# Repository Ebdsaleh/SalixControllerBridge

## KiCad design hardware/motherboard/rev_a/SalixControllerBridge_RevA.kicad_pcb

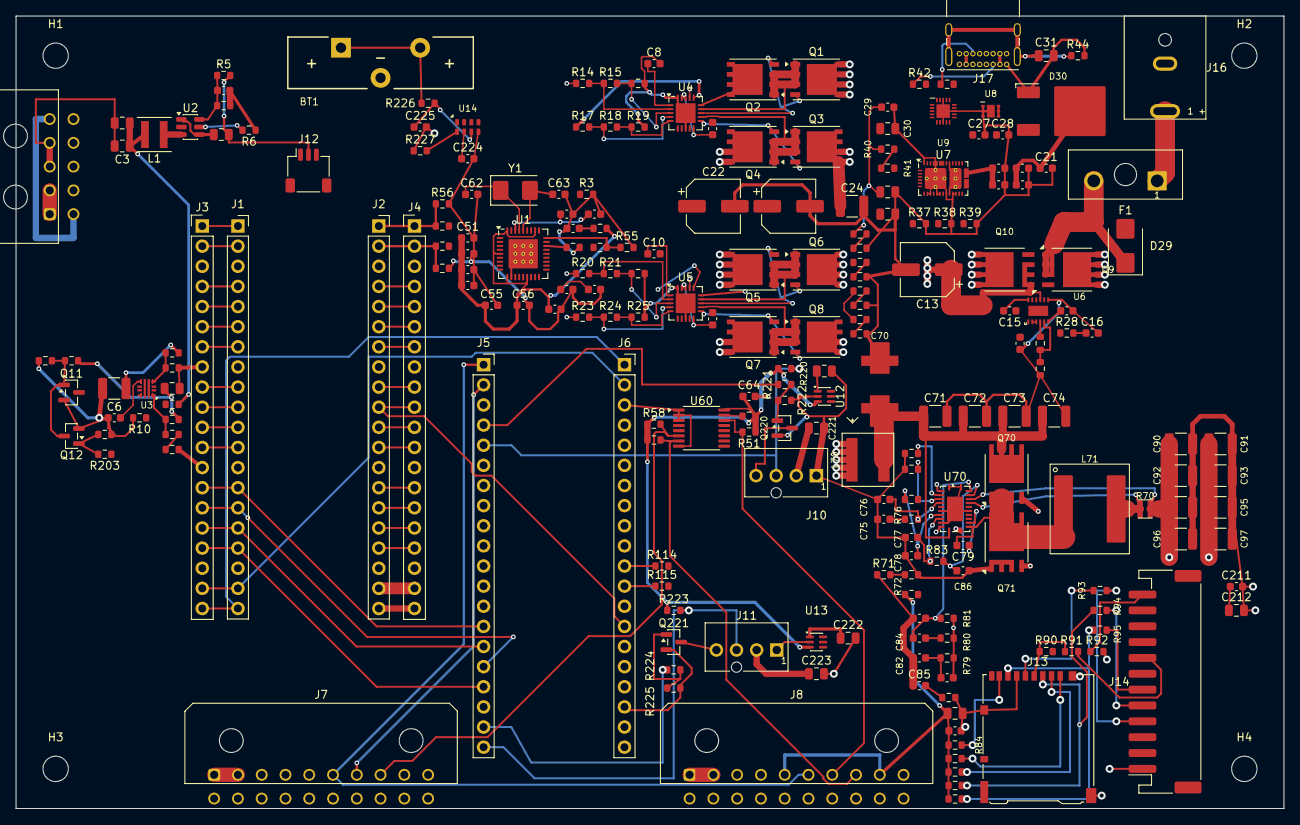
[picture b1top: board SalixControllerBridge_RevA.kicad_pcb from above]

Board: 4 copper layers, 160.0 x 100.0 mm, 230 parts (0 on the bottom side), 187 nets.

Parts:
BT1: CR2032; Keystone_1174_CR2032_Vertical_Exact
C1: 4.7uF 10V X7R; C_0805_2012Metric
C2, C3: 22uF 10V X7R; C_0805_2012Metric
C4: 6.8pF; C_0603_1608Metric
C5: 1uF 35V X7R; C_0805_2012Metric
C6: 10uF 35V X7R; C_1210_3225Metric
C7: 3.3nF 50V; C_0603_1608Metric
C8, C10: 1nF 50V; C_0603_1608Metric
C9, C11: 100nF 10V X7R; C_0603_1608Metric
C12, C14: 100nF 100V X7R; C_0603_1608Metric
C13: EEETQV470XAP 47uF 35V; CP_Elec_6.3x7.7
C15: 100nF 25V X7R; C_0603_1608Metric
C16: 10nF 50V X7R; C_0603_1608Metric
C17: 4.7uF 35V X5R +/-10%; C_0603_1608Metric
C18, C19, C20, C21: 10nF 50V X7R +/-5%; C_0603_1608Metric
C22, C23: 33uF 50V HYBRID +/-20%; CP_Elec_6.3x7.7
C24: 10uF 50V X7R +/-10%; C_1210_3225Metric
C25, C26: 10uF 10V X7R +/-10%; C_0805_2012Metric
C27, C28: 330pF C0G; C_0603_1608Metric
C29: 1uF 35V X5R +/-10%; C_0603_1608Metric
C30, C31: 100nF 100V X7R +/-10%; C_0805_2012Metric
C50: 1uF 10V X7R; C_0603_1608Metric
C51, C52, C53, C54, C56, C57: 100nF X7R; C_0603_1608Metric
C55: 1uF X7R; C_0603_1608Metric
C58, C60: DNP; C_0603_1608Metric
C59, C61: 100nF low-ESR; C_0603_1608Metric
C62, C63: CC0603JRNPO9BN180 18pF C0G; C_0603_1608Metric
C64, C80, C211, C224, C225: 100nF; C_0603_1608Metric
C70: 100uF 35V hybrid; Panasonic_EEH_ZC_F_VibrationProof_8x10.5mm
C71, C72, C73, C74: 10uF 50V X7S; C_1210_3225Metric
C75: 10nF; C_0603_1608Metric
C76: 22pF DNP; C_0603_1608Metric
C77: 2.2uF; C_0603_1608Metric
C78, C79: 0.1uF; C_0603_1608Metric
C81: 0.1uF CSEN; C_0603_1608Metric
C82: 0.47uF CINJ; C_0603_1608Metric
C83: 0.22uF CDAMP; C_0603_1608Metric
C84: 1nF CAEFC; C_0603_1608Metric
C85: 0.1uF CINC; C_0603_1608Metric
C86: 2.2uF CAEFVDD; C_0603_1608Metric
C90, C91, C92, C93, C94, C95, C96, C97: 47uF 10V X7S; C_1210_3225Metric
C210, C212, C221, C223: 10uF; C_0805_2012Metric
C220, C222: 1uF; C_0805_2012Metric
D29: SMBJ36CA; D_SMB
D30: STPS5H100BY-TR; ST_DPAK_STPS5H100Y
F1: MINI FL1 HOLDER / 7.5A PROVISIONAL; Littelfuse_178.6764.0001_MINI_FL1
H1, H2, H3, H4: Salix_MountingHole_3.2mm_M3
J1: PICO-A SOCKET LEFT 1-20; PinSocket_1x20_P2.54mm_Vertical
J2: PICO-A SOCKET RIGHT 21-40; Salix_PinSocket_1x20_P2.54mm_Vertical_P21-40
J3: RAW BREAKOUT 1-20; PinHeader_1x20_P2.54mm_Vertical
J4: RAW BREAKOUT 21-40; Salix_PinHeader_1x20_P2.54mm_Vertical_P21-40
J5: PICO-B SOCKET LEFT 1-20; PinSocket_1x20_P2.54mm_Vertical
J6: PICO-B SOCKET RIGHT 21-40; Salix_PinSocket_1x20_P2.54mm_Vertical_P21-40
J7: PRIMARY FRONT BOARD IF; Molex_Micro-Fit_3.0_43045-2000_2x10_P3.00mm_Horizontal
J8: EXTENDED FRONT BOARD IF; Molex_Micro-Fit_3.0_43045-2000_2x10_P3.00mm_Horizontal
J10: FAN0 — MOLEX 47053-1000; Molex_47053-1000_1x04_P2.54mm_Vertical
J11: FAN1 — MOLEX 47053-1000; Molex_47053-1000_1x04_P2.54mm_Vertical
J12: PICO-A SWD JST-SH; JST_SH_SM03B-SRSS-TB_1x03-1MP_P1.00mm_Horizontal
J13: HIROSE DM3AT-SF-PEJM5; Hirose_DM3AT-SF-PEJM5_Exact
J14: JST S12B-PH-SM4-TB; JST_PH_S12B-PH-SM4-TB_1x12-1MP_P2.00mm_Horizontal
J15: AUX POWER MODULE — MOLEX 43045-1000; Molex_Micro-Fit_3.0_43045-1000_2x05_P3.00mm_Horizontal
J16: KLDHCX-8-0202-B; Kycon_KLDHCX-8-0202-B
J17: USB-C PD POWER — GCT USB4085-GF-A; GCT_USB4085_Exact
L1: XAL4020-222ME 2.2uH; L_Coilcraft_XxL4020
L70: XGL6060-102MEC 1.0uH; Coilcraft_XGL6060_6.71x6.51mm
L71: XGL1010-222MED 2.2uH; Coilcraft_XGL1010_11.3x10.0mm
Q1, Q2, Q3, Q4, Q5, Q6, Q7, Q8: Si7155DP-T1-GE3; Vishay_PowerPAK_SO-8_Single
Q9, Q10: IAUC100N08S5N034ATMA1; Infineon_PG_TDSON_8_34
Q11, Q12: 2N7002BK,215; SOT-23
Q70, Q71: IAUC60N04S6L039; Infineon_PG_TDSON_8_33
Q220, Q221: 2N7002; SOT-23
R1, R2: 22R 1%; R_0603_1608Metric
R3: 12.0k 1%; R_0603_1608Metric
R4: 453k 1%; R_0603_1608Metric
R5, R13, R52, R54, R55, R200, R201, R202: 100k 1%; R_0603_1608Metric
R6: 100k PG pull-up; R_0603_1608Metric
R7: 464k 1%; R_0603_1608Metric
R8: 52.3k 1%; R_0603_1608Metric
R9, R18: 30.1k 1%; R_0603_1608Metric
R10: 1.33k 1%; R_0603_1608Metric
R11, R16, R24: 56.2k 1%; R_0603_1608Metric
R12, R53, R203: 10k 1%; R_0603_1608Metric
R14, R20, R23: 887k 1%; R_0603_1608Metric
R15: 61.9k 1%; R_0603_1608Metric
R17: 931k 1%; R_0603_1608Metric
R19, R22: 44.2k 1%; R_0603_1608Metric
R21: 80.6k 1%; R_0603_1608Metric
R25: 60.4k 1%; R_0603_1608Metric
R26: 93.1k 1%; R_0603_1608Metric
R27: 6.19k 1%; R_0603_1608Metric
R28: 100R 1%; R_0603_1608Metric
R29, R32, R33, R35: 162k 1%; R_0603_1608Metric
R30, R34, R36: 38.0k 1%; R_0603_1608Metric
R31: 38.3k 1%; R_0603_1608Metric
R37, R38, R39, R40, R58, R59, R220, R223, R227: 10k; R_0603_1608Metric
R41, R42, R43: 0R; R_0603_1608Metric
R44: 330R; R_0603_1608Metric
R50, R51: 4.7k 1%; R_0603_1608Metric
R56, R57: 15k 1%; R_0603_1608Metric
R70: 3mR 1% 1W; Susumu_KRL2012E_0508_LongSide
R71, R74: 49.9k 1%; R_0603_1608Metric
R72: 8.06k 1%; R_0603_1608Metric
R73: 24.9k 1%; R_0603_1608Metric
R75: 41.2k 1%; R_0603_1608Metric
R76: 5.90k 1%; R_0603_1608Metric
R78, R92, R222, R225: 100k; R_0603_1608Metric
R79: 17.8R RDAMP; R_0603_1608Metric
R80: 1k RAEFC; R_0603_1608Metric
R81: 49.9k RAEFDC; R_0603_1608Metric
R82: 0.47R RINC; R_0603_1608Metric
R83: 3R RAEFVDD; R_0603_1608Metric
R84, R90, R91, R210, R211, R212, R213: 47k; R_0603_1608Metric
R93, R94, R95: 33R; R_0603_1608Metric
R114, R115: 100R; R_0603_1608Metric
R221, R224: 1k; R_0603_1608Metric
R226: 470R; R_0603_1608Metric
U1: USB2514B/M2; QFN-36-1EP_6x6mm_P0.5mm_EP3.7x3.7mm_ThermalVias
U2: TLV62569P; SOT-23-6
U3: TPS259474LRPWR; TI_RPW0010A_VQFN-HR-10_2x2mm_P0.475mm
U4, U5: LTC4418IUF#PBF; QFN-20-1EP_4x4mm_P0.5mm_EP2.5x2.5mm
U6: LM74800QDRRRQ1; TI_DRR0012E_WSON-12_3x3mm_P0.5mm_FloatingEP
U7: TPS25730ADREFR; TI_REF0038A_WQFN-38-2EP_6x4mm_P0.4
U8: TVS2200DRVR; TI_DRV0006A_WSON-6_2x2mm_P0.65mm_EP1x1.6mm
U9: TPD4S201RUKR; TI_RUK0020B_WQFN-20_3x3mm_P0.4mm_EP1.7x1.7mm
U12, U13: TPS22919DCK; SOT-363_SC-70-6
U14: RV-3028-C7; MicroCrystal_RV-3028-C7
U60: TCA9534APWR; TSSOP-16_4.4x5mm_P0.65mm
U70: LM25149QRGYRQ1; Texas_RGY_R-PVQFN-N24_EP2.05x3.1mm
Y1: CTS 445I25A24M00000 24MHz 10pF; Crystal_SMD_5032-2Pin_5.0x3.2mm

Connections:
3V3_AUX: C2.1, C3.1, C4.1, C51.1, C52.1, C53.1, C54.1, C55.1, C56.1, C57.1, C64.1, C80.1, C210.1, C211.1, C212.1, C224.1, J7.5 (3V3_AUX), J8.5 (3V3_AUX), J8.9 (BOARD_ID), J13.4 (VDD), J14.2 (3V3_LOGIC), L1.2, R4.1, R6.1, R13.2, R50.1, R51.1, R53.1, R58.1, R59.1, R78.1, R84.1, R90.1, R91.1, R210.1, R211.1, R212.1, R213.1, R220.1, R223.1, U1.5 (VDDA33), U1.10 (VDDA33), U1.15 (VDD33), U1.23 (VDD33), U1.29 (VDDA33), U1.36 (VDDA33), U12.3 (ON), U13.3 (ON), U14.7 (VDD), U60.16 (VCC)
3V3_AUX_PG: R6.2, U2.5 (PG)
5V_MAIN: C1.1, C90.1, C91.1, C92.1, C93.1, C94.1, C95.1, C96.1, C97.1, C220.1, C222.1, J2.39 (VSYS), J4.39 (VSYS), J6.39 (VSYS), J7.1 (5V_A), J7.2 (5V_B), J8.1 (5V_A), J8.2 (5V_B), J14.3 (5V_AUX), R54.1, R70.2, U2.1 (EN), U2.4 (VIN), U12.1 (IN), U13.1 (IN), U70.16 (VCCX), U70.21 (VOUT)
5V_MAIN_PGOOD: R78.2, U70.17 (PG/SYNCOUT)
/5V_MAIN / 12A SYNCHRONOUS BUCK/AEF_COMP_MID: C84.2, R80.1
/5V_MAIN / 12A SYNCHRONOUS BUCK/AEF_DAMP_TOP: C82.2, C83.1, R79.1
/5V_MAIN / 12A SYNCHRONOUS BUCK/AEF_RINC_MID: C85.2, R82.1
/5V_MAIN / 12A SYNCHRONOUS BUCK/BUCK_AEFVDDA: C86.1, R83.2, U70.22 (AEFVDDA)
/5V_MAIN / 12A SYNCHRONOUS BUCK/BUCK_CBOOT: C79.1, U70.15 (CBOOT)
/5V_MAIN / 12A SYNCHRONOUS BUCK/BUCK_CNFG: R75.1, U70.3 (CNFG)
/5V_MAIN / 12A SYNCHRONOUS BUCK/BUCK_COMP: C76.1, R76.1, U70.5 (EXTCOMP)
/5V_MAIN / 12A SYNCHRONOUS BUCK/BUCK_COMP_RC: C75.1, R76.2
/5V_MAIN / 12A SYNCHRONOUS BUCK/BUCK_EN: R71.2, R72.1, U70.19 (EN)
/5V_MAIN / 12A SYNCHRONOUS BUCK/BUCK_FB: R73.2, U70.6 (FB)
/5V_MAIN / 12A SYNCHRONOUS BUCK/BUCK_HO: Q70.4 (G), U70.13 (HO)
/5V_MAIN / 12A SYNCHRONOUS BUCK/BUCK_INJ: C83.2, R79.2, R80.2, R81.2, U70.2 (INJ)
/5V_MAIN / 12A SYNCHRONOUS BUCK/BUCK_ISNS_PLUS: L71.2, R70.1, U70.20 (ISNS+)
/5V_MAIN / 12A SYNCHRONOUS BUCK/BUCK_LO: Q71.4 (G), U70.11 (LO)
/5V_MAIN / 12A SYNCHRONOUS BUCK/BUCK_RT: R74.1, U70.4 (RT)
/5V_MAIN / 12A SYNCHRONOUS BUCK/BUCK_SEN: C81.2, C84.1, R81.1, U70.23 (SEN)
/5V_MAIN / 12A SYNCHRONOUS BUCK/BUCK_SW: C79.2, L71.1, Q70.1 (S), Q70.2 (S), Q70.3 (S), Q71.5 (D), Q71.6 (D), Q71.7 (D), Q71.8 (D), U70.14 (SW)
/5V_MAIN / 12A SYNCHRONOUS BUCK/BUCK_VCC: C77.1, R83.1, U70.9 (VCC)
/5V_MAIN / 12A SYNCHRONOUS BUCK/BUCK_VDDA: C78.1, R73.1, U70.8 (VDDA)
/5V_MAIN / 12A SYNCHRONOUS BUCK/BUCK_VIN: C70.1, C71.1, C72.1, C73.1, C74.1, L70.2, Q70.5 (D), Q70.6 (D), Q70.7 (D), Q70.8 (D), U70.12 (VIN)
/12V BARREL / AUTOMOTIVE FRONT END/BARREL_CAP: C15.1, U6.11 (CAP)
/12V BARREL / AUTOMOTIVE FRONT END/BARREL_DGATE: Q9.4 (G), U6.1 (DGATE)
/12V BARREL / AUTOMOTIVE FRONT END/BARREL_DVDT: C16.1, R28.2
/12V BARREL / AUTOMOTIVE FRONT END/BARREL_FUSED: C12.1, D29.1 (A1), F1.2, Q9.1 (S), Q9.2 (S), Q9.3 (S), U6.2 (A), U6.3 (VSNS)
/12V BARREL / AUTOMOTIVE FRONT END/BARREL_HGATE: Q10.4 (G), R28.1, U6.8 (HGATE)
/12V BARREL / AUTOMOTIVE FRONT END/BARREL_JACK_RAW: F1.1, J16.1 (CENTER_+)
/12V BARREL / AUTOMOTIVE FRONT END/BARREL_MID: C14.1, C15.2, Q9.5 (D), Q9.6 (D), Q9.7 (D), Q9.8 (D), Q10.5 (D), Q10.6 (D), Q10.7 (D), Q10.8 (D), U6.6 (EN/UVLO), U6.10 (VS), U6.12 (C)
/12V BARREL / AUTOMOTIVE FRONT END/BARREL_OV: R26.2, R27.1, U6.5 (OV)
/12V BARREL / AUTOMOTIVE FRONT END/BARREL_OV_TOP: R26.1, U6.4 (SW)
/MAIN SOURCE PRIORITY / POWERPATH/U4_G1: Q1.4 (G), Q2.4 (G), U4.13 (G1)
/MAIN SOURCE PRIORITY / POWERPATH/U4_G2: Q3.4 (G), Q4.4 (G), U4.11 (G2)
/MAIN SOURCE PRIORITY / POWERPATH/U4_INTVCC: C9.1, U4.10 (INTVCC), U4.18 (EN), U4.19 (SHDN)
/MAIN SOURCE PRIORITY / POWERPATH/U4_OV1: R15.2, R16.1, U4.3 (OV1)
/MAIN SOURCE PRIORITY / POWERPATH/U4_OV2: R18.2, R19.1, U4.5 (OV2)
/MAIN SOURCE PRIORITY / POWERPATH/U4_TMR: C8.1, U4.1 (TMR)
/MAIN SOURCE PRIORITY / POWERPATH/U4_UV1: R14.2, R15.1, U4.2 (UV1)
/MAIN SOURCE PRIORITY / POWERPATH/U4_UV2: R17.2, R18.1, U4.4 (UV2)
/MAIN SOURCE PRIORITY / POWERPATH/U4_VS1: Q1.1 (S), Q1.2 (S), Q1.3 (S), Q2.1 (S), Q2.2 (S), Q2.3 (S), U4.14 (VS1)
/MAIN SOURCE PRIORITY / POWERPATH/U4_VS2: Q3.1 (S), Q3.2 (S), Q3.3 (S), Q4.1 (S), Q4.2 (S), Q4.3 (S), U4.12 (VS2)
/MAIN SOURCE PRIORITY / POWERPATH/U5_G1: Q5.4 (G), Q6.4 (G), U5.13 (G1)
/MAIN SOURCE PRIORITY / POWERPATH/U5_G2: Q7.4 (G), Q8.4 (G), U5.11 (G2)
/MAIN SOURCE PRIORITY / POWERPATH/U5_INTVCC: C11.1, U5.10 (INTVCC), U5.18 (EN), U5.19 (SHDN)
/MAIN SOURCE PRIORITY / POWERPATH/U5_OV1: R21.2, R22.1, U5.3 (OV1)
/MAIN SOURCE PRIORITY / POWERPATH/U5_OV2: R24.2, R25.1, U5.5 (OV2)
/MAIN SOURCE PRIORITY / POWERPATH/U5_TMR: C10.1, U5.1 (TMR)
/MAIN SOURCE PRIORITY / POWERPATH/U5_UV1: R20.2, R21.1, U5.2 (UV1)
/MAIN SOURCE PRIORITY / POWERPATH/U5_UV2: R23.2, R24.1, U5.4 (UV2)
/MAIN SOURCE PRIORITY / POWERPATH/U5_VS1: Q5.1 (S), Q5.2 (S), Q5.3 (S), Q6.1 (S), Q6.2 (S), Q6.3 (S), U5.14 (VS1)
/MAIN SOURCE PRIORITY / POWERPATH/U5_VS2: Q7.1 (S), Q7.2 (S), Q7.3 (S), Q8.1 (S), Q8.2 (S), Q8.3 (S), U5.12 (VS2)
/PICO-B SERVICE / STORAGE / UI/SD_DAT1: J13.8 (DAT1/RSV), R84.2
/PICO-B SERVICE / STORAGE / UI/SD_DAT2: J13.1 (DAT2/RSV), R210.2
/PICO-B SERVICE / STORAGE / UI/TFT_SPI_MISO: J14.6 (SPI_MISO), R95.2
/PICO-B SERVICE / STORAGE / UI/TFT_SPI_MOSI: J14.5 (SPI_MOSI), R94.2
/PICO-B SERVICE / STORAGE / UI/TFT_SPI_SCK: J14.4 (SPI_SCK), R93.2
/POWER / PROTECTION/AUX_CHG_CTL_GATE: Q12.1 (G), R202.1, R203.2
/POWER / PROTECTION/AUX_CHG_DIS_BIAS: Q11.1 (G), Q12.3 (D), R200.2, R201.1
/POWER / PROTECTION/AUX_DVDT: C7.1, U3.7 (DVDT)
/POWER / PROTECTION/AUX_ILM: R10.1, U3.9 (ILM)
/POWER / PROTECTION/AUX_OV_SENSE: R8.2, R9.1, U3.2 (OVLO)
/POWER / PROTECTION/AUX_PGTH: R11.2, R12.1, U3.4 (PGTH)
/POWER / PROTECTION/AUX_UV_SENSE: Q11.3 (D), R7.2, R8.1, U3.1 (EN/UVLO)
/POWER / PROTECTION/BUCK_FB: C4.2, R4.2, R5.1, U2.6 (FB)
/SERVICE / DEBUG / SUPERVISION/FAN0_5V: C221.1, J10.2 (+5V_FAN), U12.6 (VOUT)
/SERVICE / DEBUG / SUPERVISION/FAN0_PWM_GATE: Q220.1 (G), R221.2, R222.1
/SERVICE / DEBUG / SUPERVISION/FAN0_PWM_OD: J10.4 (PWM_EN), Q220.3 (D)
/SERVICE / DEBUG / SUPERVISION/FAN1_5V: C223.1, J11.2 (+5V_FAN), U13.6 (VOUT)
/SERVICE / DEBUG / SUPERVISION/FAN1_PWM_GATE: Q221.1 (G), R224.2, R225.1
/SERVICE / DEBUG / SUPERVISION/FAN1_PWM_OD: J11.4 (PWM_EN), Q221.3 (D)
/SERVICE / DEBUG / SUPERVISION/RTC_BAT_RAW: BT1.1 (+), R226.1
/SERVICE / DEBUG / SUPERVISION/RTC_EVI: R227.2, U14.8 (EVI)
/SERVICE / DEBUG / SUPERVISION/RTC_VBAT: C225.1, R226.2, U14.6 (VBACKUP)
/USB HUB / INPUT INTERFACE/EXTENDED_ENABLE_N: J8.10 (BOARD_ENABLE_N), U60.5 (P1)
/USB HUB / INPUT INTERFACE/EXTENDED_INT_N: J8.8 (INT_N), R59.2, U60.7 (P3)
/USB HUB / INPUT INTERFACE/HUB_CRFILT: C58.1, C59.1, U1.14 (CRFILT)
/USB HUB / INPUT INTERFACE/HUB_HS_IND: R52.1, U1.25 (HS_IND/CFG_SEL1)
/USB HUB / INPUT INTERFACE/HUB_OCS1_N: J7.14 (BANK_A_OCS_N), U1.13 (OCS_N1)
/USB HUB / INPUT INTERFACE/HUB_OCS2_N: J7.18 (BANK_B_OCS_N), U1.17 (OCS_N2)
/USB HUB / INPUT INTERFACE/HUB_OCS3_N: J8.14 (BANK_A_OCS_N), U1.19 (OCS_N3)
/USB HUB / INPUT INTERFACE/HUB_OCS4_N: J8.18 (BANK_B_OCS_N), U1.21 (OCS_N4)
/USB HUB / INPUT INTERFACE/HUB_PLLFILT: C60.1, C61.1, U1.34 (PLLFILT)
/USB HUB / INPUT INTERFACE/HUB_PRTPWR1: J7.13 (BANK_A_PRTPWR), U1.12 (PRTPWR1/BC_EN1)
/USB HUB / INPUT INTERFACE/HUB_PRTPWR2: J7.17 (BANK_B_PRTPWR), U1.16 (PRTPWR2/BC_EN2)
/USB HUB / INPUT INTERFACE/HUB_PRTPWR3: J8.13 (BANK_A_PRTPWR), U1.18 (PRTPWR3/BC_EN3)
/USB HUB / INPUT INTERFACE/HUB_PRTPWR4: J8.17 (BANK_B_PRTPWR), U1.20 (PRTPWR4/BC_EN4)
/USB HUB / INPUT INTERFACE/HUB_RBIAS: R3.1, U1.35 (RBIAS)
/USB HUB / INPUT INTERFACE/HUB_USBDM_UP: R2.1, U1.30 (USBDM_UP)
/USB HUB / INPUT INTERFACE/HUB_USBDP_UP: R1.1, U1.31 (USBDP_UP)
/USB HUB / INPUT INTERFACE/HUB_VBUS_DET: R54.2, R55.1, U1.27 (VBUS_DET)
/USB HUB / INPUT INTERFACE/HUB_XTALIN: C62.1, U1.33 (XTALIN/CLKIN), Y1.1
/USB HUB / INPUT INTERFACE/HUB_XTALOUT: C63.1, U1.32 (XTALOUT), Y1.2
/USB HUB / INPUT INTERFACE/PRIMARY_ENABLE_N: J7.10 (BOARD_ENABLE_N), U60.4 (P0)
/USB HUB / INPUT INTERFACE/PRIMARY_INT_N: J7.8 (INT_N), R58.2, U60.6 (P2)
/USB HUB / INPUT INTERFACE/USB_DN1_DM: J7.11 (BANK_A_DM), U1.1 (USBDM_DN1/PRT_DIS_M1)
/USB HUB / INPUT INTERFACE/USB_DN1_DP: J7.12 (BANK_A_DP), U1.2 (USBDP_DN1/PRT_DIS_P1)
/USB HUB / INPUT INTERFACE/USB_DN2_DM: J7.15 (BANK_B_DM), U1.3 (USBDM_DN2/PRT_DIS_M2)
/USB HUB / INPUT INTERFACE/USB_DN2_DP: J7.16 (BANK_B_DP), U1.4 (USBDP_DN2/PRT_DIS_P2)
/USB HUB / INPUT INTERFACE/USB_DN3_DM: J8.11 (BANK_A_DM), U1.6 (USBDM_DN3/PRT_DIS_M3)
/USB HUB / INPUT INTERFACE/USB_DN3_DP: J8.12 (BANK_A_DP), U1.7 (USBDP_DN3/PRT_DIS_P3)
/USB HUB / INPUT INTERFACE/USB_DN4_DM: J8.15 (BANK_B_DM), U1.8 (USBDM_DN4/PRT_DIS_M4)
/USB HUB / INPUT INTERFACE/USB_DN4_DP: J8.16 (BANK_B_DP), U1.9 (USBDP_DN4/PRT_DIS_P4)
/USB-C PD POWER INPUT/PD5VMAX: R37.1, U7.27 (PD5VMAX)
/USB-C PD POWER INPUT/PD_ADC1: R29.2, R30.1, U7.2 (ADCIN1)
/USB-C PD POWER INPUT/PD_ADC2: R31.2, R32.1, U7.3 (ADCIN2)
/USB-C PD POWER INPUT/PD_ADC3: R33.2, R34.1, U7.5 (ADCIN3)
/USB-C PD POWER INPUT/PD_ADC4: R35.2, R36.1, U7.7 (ADCIN4)
/USB-C PD POWER INPUT/PD_CC1_CONN: J17.A5 (CC1), R42.1, U9.4 (C_CC1)
/USB-C PD POWER INPUT/PD_CC1_SYS: C27.1, U7.28 (CC1), U9.12 (CC1)
/USB-C PD POWER INPUT/PD_CC2_CONN: J17.B5 (CC2), R43.1, U9.5 (C_CC2)
/USB-C PD POWER INPUT/PD_CC2_SYS: C28.1, U7.29 (CC2), U9.11 (CC2)
/USB-C PD POWER INPUT/PD_DRAIN_FLOAT: U7.15 (DRAIN), U7.30 (DRAIN), U7.40 (DRAIN_PAD)
/USB-C PD POWER INPUT/PD_FAULT_IN: R41.2, U7.18 (FAULT_IN)
/USB-C PD POWER INPUT/PD_LDO1V5: C26.1, U7.4 (LDO_1V5)
/USB-C PD POWER INPUT/PD_LDO3V3: C25.1, C29.1, R29.1, R31.1, R33.1, R35.1, R40.1, U7.1 (LDO_3V3), U9.10 (VPWR)
/USB-C PD POWER INPUT/PD_RESERVED26: R38.1, U7.26 (RESERVED26)
/USB-C PD POWER INPUT/PD_RESERVED36: R39.1, U7.36 (RESERVED36)
/USB-C PD POWER INPUT/PD_RPD_G1: R42.2, U9.7 (RPD_G1)
/USB-C PD POWER INPUT/PD_RPD_G2: R43.2, U9.6 (RPD_G2)
/USB-C PD POWER INPUT/PD_SHIELD: C31.1, J17.S1 (SHIELD), R44.1
/USB-C PD POWER INPUT/PD_TPD_FLT: R40.2, R41.1, U9.9 (FLT)
/USB-C PD POWER INPUT/PD_TPD_VBIAS: C30.1, U9.3 (VBIAS)
/USB-C PD POWER INPUT/PD_VBUS_RAW: C17.1, C18.1, C19.1, C20.1, C21.1, D30.2 (K), J17.A4 (VBUS), J17.A9 (VBUS), J17.B4 (VBUS), J17.B9 (VBUS), U7.23 (VBUS_IN), U7.32 (VBUS), U8.4 (IN), U8.5 (IN), U8.6 (IN)
AUX_CHG_ENABLE: R203.1, U60.9 (P4)
AUX_CHG_PG: R13.1, U3.3 (PG), U60.10 (P5)
AUX_PWR: J15.1 (AUX_PWR_A), J15.2 (AUX_PWR_B), Q7.5 (D), R23.1, U5.16 (V2)
BARREL_PROT: C13.1, Q1.5 (D), Q10.1 (S), Q10.2 (S), Q10.3 (S), R14.1, U4.17 (V1), U6.9 (OUT)
CHARGE_PWR: C6.1, J15.5 (CHARGE_PWR_A), J15.6 (CHARGE_PWR_B), R11.1, U3.6 (OUT)
EXT_CHARGE_IN: C5.1, Q2.5 (D), Q4.5 (D), Q5.5 (D), R7.1, R20.1, R200.1, U3.5 (IN), U4.15 (VOUT), U5.17 (V1)
FAN0_PWM_EN: J5.4 (GP2), R221.1
FAN0_TACH: J5.5 (GP3), J10.3 (TACH), R220.2
FAN1_PWM_EN: J5.19 (GP14), R224.1
FAN1_TACH: J5.20 (GP15), J11.3 (TACH), R223.2
GND: BT1.2 (-), C1.2, C2.2, C3.2, C5.2, C6.2, C7.2, C8.2, C9.2, C10.2, C11.2, C12.2, C13.2, C14.2, C16.2, C17.2, C18.2, C19.2, C20.2, C21.2, C22.2 (-), C23.2 (-), C24.2, C25.2, C26.2, C27.2, C28.2, C29.2, C30.2, C31.2, C50.2, C51.2, C52.2, C53.2, C54.2, C55.2, C56.2, C57.2, C58.2, C59.2, C60.2, C61.2, C62.2, C63.2, C64.2, C70.2, C71.2, C72.2, C73.2, C74.2, C75.2, C76.2, C77.2, C78.2, C80.2, C86.2, C90.2, C91.2, C92.2, C93.2, C94.2, C95.2, C96.2, C97.2, C210.2, C211.2, C212.2, C220.2, C221.2, C222.2, C223.2, C224.2, C225.2, D29.2 (A2), D30.1 (A), J1.3 (GND), J1.8 (GND), J1.13 (GND), J1.18 (GND), J2.23 (GND), J2.28 (GND), J2.33 (AGND), J2.38 (GND), J3.3 (GND), J3.8 (GND), J3.13 (GND), J3.18 (GND), J4.23 (GND), J4.28 (GND), J4.33 (AGND), J4.38 (GND), J5.3 (GND), J5.8 (GND), J5.13 (GND), J5.18 (GND), J6.23 (GND), J6.28 (GND), J6.33 (AGND), J6.38 (GND), J7.3 (GND_A), J7.4 (GND_B), J7.9 (BOARD_ID), J7.19 (GND_C), J7.20 (GND_D), J8.3 (GND_A), J8.4 (GND_B), J8.19 (GND_C), J8.20 (GND_D), J10.1 (GND), J11.1 (GND), J12.2 (GND), J13.6 (VSS), J13.11 (SHIELD), J14.1 (GND), J15.3 (GND_A), J15.4 (GND_B), J16.2 (SLEEVE_GND), J17.A1 (GND), J17.A12 (GND), J17.B1 (GND), J17.B12 (GND), Q11.2 (S), Q12.2 (S), Q71.1 (S), Q71.2 (S), Q71.3 (S), Q220.2 (S), Q221.2 (S), R3.2, R5.2, R9.2, R10.2, R12.2, R16.2, R19.2, R22.2, R25.2, R27.2, R30.2, R32.2, R34.2, R36.2, R37.2, R38.2, R39.2, R44.2, R52.2, R55.2, R56.2, R57.2, R72.2, R74.2, R75.2, R82.2, R92.2, R201.2, R202.2, R222.2, R225.2, R227.1, U1.11 (TEST), U1.37 (VSS_EP), U2.2 (GND), U3.8 (GND), U4.8 (GND), U4.20 (HYS), U4.21 (EP_GND), U5.8 (GND), U5.20 (HYS), U5.21 (EP_GND), U6.7 (GND), U7.8 (I2Ct_SDA), U7.9 (I2Ct_SCL), U7.11 (GND), U7.12 (GND), U7.14 (GND), U7.16 (GND), U7.17 (GND), U7.31 (GND), U7.34 (GND), U7.38 (VIN_3V3), U7.39 (GND_PAD), U8.1 (GND), U8.2 (GND), U8.3 (GND), U8.7 (GND_PAD), U9.8 (GND), U9.13 (GND), U9.18 (GND), U9.21 (GND_PAD), U12.2 (GND), U13.2 (GND), U14.5 (VSS), U60.1 (A0), U60.2 (A1), U60.3 (A2), U60.8 (GND), U70.1 (AVSS), U70.7 (AGND), U70.10 (PGND), U70.18 (PFM/SYNC), U70.24 (REFAGND), U70.25 (EP)
HUB_RESET_N: C50.1, J6.29 (GP22), R53.2, U1.26 (RESET_N)
IRQ_A2B: J1.19 (GP14), J3.19 (GP14), J6.22 (GP17)
IRQ_B2A: J1.20 (GP15), J3.20 (GP15), J6.21 (GP16)
MGMT_I2C_SCL: J5.2 (GP1), J7.7 (I2C_SCL), J8.7 (I2C_SCL), R51.2, U1.24 (SCL/SMBCLK/CFG_SEL0), U14.3 (SCL), U60.14 (SCL)
MGMT_I2C_SDA: J5.1 (GP0), J7.6 (I2C_SDA), J8.6 (I2C_SDA), R50.2, U1.22 (SDA/SMBDATA/NON_REM1), U14.4 (SDA), U60.15 (SDA)
unnamed: J1.1 (GP0), J3.1 (GP0)
unnamed: J1.2 (GP1), J3.2 (GP1)
unnamed: J1.4 (GP2), J3.4 (GP2)
unnamed: J1.5 (GP3), J3.5 (GP3)
unnamed: J1.6 (GP4), J3.6 (GP4)
unnamed: J1.7 (GP5), J3.7 (GP5)
unnamed: J1.9 (GP6), J3.9 (GP6)
unnamed: J1.10 (GP7), J3.10 (GP7)
unnamed: J1.11 (GP8), J3.11 (GP8)
unnamed: J1.12 (GP9), J3.12 (GP9)
unnamed: J2.37 (3V3_EN), J4.37 (3V3_EN)
unnamed: J2.36 (3V3_OUT), J4.36 (3V3_OUT)
unnamed: J2.35 (ADC_VREF), J4.35 (ADC_VREF)
unnamed: J2.24 (GP18), J4.24 (GP18)
unnamed: J2.25 (GP19), J4.25 (GP19)
unnamed: J2.26 (GP20), J4.26 (GP20)
unnamed: J2.27 (GP21), J4.27 (GP21)
unnamed: J2.29 (GP22), J4.29 (GP22)
unnamed: J2.31 (GP26), J4.31 (GP26)
unnamed: J2.32 (GP27), J4.32 (GP27)
unnamed: J2.34 (GP28), J4.34 (GP28)
unnamed: J2.40 (VBUS), J4.40 (VBUS)
unnamed: J6.31 (GP26), R114.1
unnamed: J6.32 (GP27), R115.1
unnamed: L1.1, U2.3 (SW)
PD_PWR: C22.1 (+), C23.1 (+), C24.1, Q3.5 (D), R17.1, U4.16 (V2), U7.20 (PPHV)
PICO_A_GP16_USB_DP: J2.21 (GP16), J4.21 (GP16), R1.2, R56.1
PICO_A_GP17_USB_DM: J2.22 (GP17), J4.22 (GP17), R2.2, R57.1
PICO_A_RUN: J2.30 (RUN), J4.30 (RUN), J6.34 (GP28)
PICO_A_SWCLK: J12.1 (SWCLK), R115.2
PICO_A_SWDIO: J12.3 (SWDIO), R114.2
RPC_CS_N: J1.17 (GP13), J3.17 (GP13), J5.17 (GP13)
RPC_MISO: J1.16 (GP12), J3.16 (GP12), J5.15 (GP11)
RPC_MOSI: J1.15 (GP11), J3.15 (GP11), J5.16 (GP12)
RPC_SCK: J1.14 (GP10), J3.14 (GP10), J5.14 (GP10)
SD_CS_N: J6.27 (GP21), J13.2 (DAT3/CS), R211.2
SERVICE_SPI_MISO: J6.26 (GP20), J13.7 (DAT0/MISO), R95.1, R213.2
SERVICE_SPI_MOSI: J6.25 (GP19), J13.3 (CMD/MOSI), R94.1, R212.2
SERVICE_SPI_SCK: J6.24 (GP18), J13.5 (CLK/SCK), R93.1
SYS_IN: C81.1, C82.1, C85.1, L70.1, Q6.5 (D), Q8.5 (D), R71.1, U5.15 (VOUT)
TFT_BL_PWM: J5.7 (GP5), J14.12 (BL_PWM_LOGIC), R92.1
TFT_DC: J5.10 (GP7), J14.9 (D_C)
TFT_LCD_CS_N: J5.12 (GP9), J14.7 (LCD_CS_N), R90.2
TFT_RESET: J5.9 (GP6), J14.10 (RESET)
TFT_TOUCH_CS_N: J5.11 (GP8), J14.8 (TOUCH_CS_N), R91.2
TFT_TOUCH_IRQ: J5.6 (GP4), J14.11 (TOUCH_IRQ)
